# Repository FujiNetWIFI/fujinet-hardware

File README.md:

# FujiNet Hardware

Hardware design files for FujiNet Retro Computer WiFi Adapter

# License

This project is released under the CERN OHL v2.0.

# Notice

Licensees must place a link to the FujiNet project github site, github.com/FujiNetWIFI OR fujinetwifi.github.io, on any product produced using these designs. Using the PCB silk screen layer is recommended for the link and is already provided on released designs.

# Certification

FujiNet hardware is certified open source by [OSHWA](https://oshwa.org). Certification details are available in the [certification directory](https://certification.oshwa.org/us000651.html) under the UID US000651.

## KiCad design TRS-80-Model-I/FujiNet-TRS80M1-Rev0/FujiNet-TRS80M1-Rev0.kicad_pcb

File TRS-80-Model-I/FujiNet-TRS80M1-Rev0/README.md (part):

# FujiNet-TRS80M1 Rev0

FujiNet for the TRS-80 Model I, in place of the Expansion Interface, on one board in a printed case.
- **RP2354B:** serves the Model I's bus (`fujinet-firmware pico/trs80m1`): 32K of RAM, the EI's interrupt latch and
  heartbeat, its printer port, an FD1771 whose drives are FujiNet slots, the RS-232 board, and the FujiBus pipe at
  D0h.
- **ESP32-S3:** the FujiNet (`fujiversal-trs80m1`) and the RP's USB host.
- **Also on the board:** a microSD, a WS2812 status light, the DIP switches that force the RAM / EI / RS-232 off,
  and a USB-C with a CP2102N bridge, the card's only power.
- **The ribbon:** a 40-wire cable from the keyboard unit's expansion edge to a right-angle box header. Every line
  meets a 3.3 V LVC buffer right at the header:
  - the strobes go through Schmitt triggers;
  - D0-D7 are driven only while RD* or IN* is low, through 75R.

**Status (2026-11-25): board routed on 4 layers, JLCPCB and PCBWay packages generated, every gate passing, printed case
drawn. Nothing has been built yet.**
- **Fixed since PR #72:**
  - PR #72 wired header pin n to edge pin n, which no straight ribbon can give: Tandy numbers the edge as the mirror
    image of an IDC connector. The header now carries the edge pins swapped in pairs (*The expansion edge and the header*).
  - The 30 bus inputs are now pulled up to +3V3_RP instead of down.
  - Don't build PR #72's files.
- **Board:** 4 layers, 100 x 76 mm, an M3 hole in each corner. Assembled by JLCPCB or PCBWay, top side: 107 SMD
  parts and the through-hole box header.
- **Firmware:** the schematic implements `pico/trs80m1/firmware/include/m1_card.h`, as it stands in the bring-up's
  dev tree (`~/Workspace/fn-trs80m1`, not on fujinet-firmware master yet). The changes it still needs are under
  *Firmware changes this board needs*.
- **Header:** checked against four sources for the Model I's expansion edge (`tools/audit/header_pinout.py`).
- **Case:** `case/`, checked in OpenSCAD against every part. Not printed yet.

| Check (2026-11-25) | Result |
|---|---|
| Drawing checks (`gen_sch.py`) | every sheet wired. Crossings: 0 on `rp-core`, `fujinet`, `power`; 1 on `usb` (esptool's auto-program pair, as on the sibling carts); 1 on `m1-bus` (the OE gate's IN* tap past RD*: `docs/design-review-rev0.md` 3) |
| Netlist parity: kicad-cli netlist vs `design.py`, names included | 127 / 127 nets |
| KiCad ERC, all severities (kicad-cli and the KiCad MCP) | 0 errors, 0 warnings |
| `tools/audit/header_pinout.py`: the 40 edge pins against the Tech Ref 26-2103 p.91, the RetroStack rev G replica, the 26-1132 HD-adapter document and TRS-IO M1; the ribbon's pair swap against Fig. 22, the HD adapter's cable table and TRS-IO M1's pad numbers; the footprint against its EasyEDA original; pin 1 on the board | 0 failures (`tools/header_geom.VERIFIED = True`) |
| `tools/check_nets.py`: the netlist vs `m1_card.h`, `fujitrs80m1_rp2354b.h`, `fujiversal-trs80m1.h` | 461 checks, 0 failed; 4 NOTE lines (the firmware changes below) |
| `tools/audit/spice/ribbon.py` (ngspice): the ribbon both ways, 15 and 45 cm | strobes never ring through the Schmitt thresholds; the 75R data drive is clean to 45 cm |
| `tools/audit/margins.py`: levels, loads, contention, read timing (in step with the firmware's `test_timing.c`), power | 27 margins, 0 negative (tightest: +23 ns, a 3.55 MHz speed-up's typical read) |
| Routing | 100 % on 4 layers; 686 vias, 1678 tracks |
| KiCad DRC + schematic parity on the saved zone fills (kicad-cli, and again through the KiCad MCP) | 0 errors, 0 unconnected, 0 parity issues; 3 silk-over-edge warnings (the S3 module's outline at the flush east edge) |
| `tools/check_vias.py`: no via in a foreign SMD pad | 686 vias, 0 failures |
| `tools/audit/layout_checks.py`: the layout's claims measured on the copper | 69 / 69. Covers the regulator corner, decoupling (every bus buffer's within 6 mm), the USB pairs and their skew, the crystal, the exposed pads, the antenna band, the buck loop, and every header line to its buffer (42.5 mm and 2 vias at most) |
| `tools/audit/check_gerbers.py`: the zip itself | 0 failures: outline, the four M3 holes, the header's 40 drills with pads and mask both sides, no copper in the antenna band, nothing past the outline, no plated hole in an In1 / In2 pour of another net (762 holes) |
| `tools/audit/check_fab.py`: JLC and PCBWay BOM / CPL / centroid / drills / order-number text / gerbers / the header gate | all pass |
| JLCPCB CPL rotations (`tools/audit/jlc/`), measured against each LCSC part's EasyEDA footprint | 46 (footprint, LCSC) pairs. The RP2354B, the box header, the DIP switch and every logic part are high confidence. Medium: the 1G11, the AOTA and buck inductors, the TS-1187A, the BAT54C, the USB-C, the TLV62569. Check those in JLC's preview |
| kicad-happy 2.2.1 (`tools/audit/run_sch_audit.sh`, `run_pcb_audit.sh`), triaged in `docs/design-review-rev0.md` | 6 high groups: 4 false positives (keep-out circles, U12 decoupling, the LDO thermal estimate at 4x the real load, the header at the edge by design), 2 accepted (plane gaps beside the header's 40 holes, USB full-speed layer changes) |
| Printed case (`case/`, OpenSCAD) | `check` and `parts_check` empty, `parts_control` not |

## Sheets

Drawn with the FujiNet-StudioII / O2 / ColecoVision toolkit:
- **Wires only:** every connection on a sheet is a wire.
- **Rails:** rails are power symbols (`GND`, `VBUS`, `+5V`, `+3V3`, `+3V3_RP`, `DVDD`).
- **Between sheets:** the sheets join only through hierarchical labels, wired on the root's block diagram.

| Page | Sheet | Contents |
|---|---|---|
| 1 | root | the block diagram: rp-core <-> fujinet (USB_DP / USB_DM, RUN_CTL, BOOTSEL_CTL, S3_EN), fujinet <-> usb (S3_TXD / S3_RXD, S3_EN, S3_IO0); notes |
| 2 | `m1-bus` (A2) | Left to right, one block per buffer group:<br>• the header (drawn in units by group) -> 100k pull-downs -> the buffer -> the RP2354B's GPIO unit for that group, every line one straight wire.<br>• A8-A15 and A0-A7: 74LVC245A, A -> B, always on.<br>• D0-D7: 75R, then the 74LVC245A turned round, DIR = DRIVE (GP28) and /OE from the 74LVC1G11 under it (DRIVE . RD* . IN*).<br>• RD* IN* INTAK* and SYSRES* OUT* WR*: two 74LVC3G17 Schmitt receivers.<br>• INT* WAIT*: the 74LVC2G07, pulled up on the RP side.<br>• The logic-analyser header, one unit per probed line.<br>• The DIP switches, LED and debug-UART pads |
| 3 | `rp-core` | the RP2354B's core unit: a capacitor at every supply pin, Raspberry Pi's regulator corner, crystal, SWD, RUN / BOOTSEL / RESET (the BAT54C to S3 EN), the USB 27R pair out to the S3 |
| 4 | `fujinet` | ESP32-S3-WROOM-1-N16R8, its EN RC and buttons, microSD, WS2812 |
| 5 | `usb` | USB-C, USBLC6-2SC6, CP2102N, esptool's auto-program pair |
| 6 | `power` | VBUS -> 1.1 A resettable fuse -> +5V; the RP's AP2112K LDO (+3V3_RP); the S3's TLV62569 buck (+3V3); rail test pads |

## The expansion edge and the header

40 contacts, two rows of 20 at 0.100", on a straight 40-wire IDC ribbon:
- **The Model I end:** a 40-way card-edge IDC connector (3M 3464-series or equivalent) on the keyboard unit's edge.
- **This board's end:** a 2x20 IDC socket on the box header.

**Tandy numbers the edge as the mirror image of that connector**, so the edge pins reach the header swapped in pairs:
header 1 = edge 2, header 2 = edge 1, header 3 = edge 4, and so on.
- Tech Ref Fig. 22, seen from the rear: odd pins on top, pin 1 at the **left**. Tandy's own EI floppy and printer
  edges have pin 1 at the top **right**.
- Buzbee / Fosdick: the expansion port "is configured opposite to other connectors on the expansion interface board".
  Plugged Tandy's way (stripe right, cable down), "the pin 1 stripe will actually connect to pin 39".
- TRS-IO M1 numbers its own edge pads the same way as this header (pad 1 SYSRES*, pad 2 RAS*).

Edge numbers are Tandy's:

| Header | Edge | Signal | Card | Header | Edge | Signal | Card |
|---|---|---|---|---|---|---|---|
| 1 | 2 | SYSRES* | 3G17 -> GP29 | 21 | 22 | D1 | 75R, '245 <-> GP17 |
| 2 | 1 | RAS* | open | 22 | 21 | INT* | GP30 -> 2G07 (OD) |
| 3 | 4 | A10 | '245 -> GP10 | 23 | 24 | D6 | 75R, '245 <-> GP22 |
| 4 | 3 | CAS* | open | 24 | 23 | TEST* | open (floats the buses) |
| 5 | 6 | A13 | '245 -> GP13 | 25 | 26 | D3 | 75R, '245 <-> GP19 |
| 6 | 5 | A12 | '245 -> GP12 | 26 | 25 | A0 | '245 -> GP0 |
| 7 | 8 | GND | GND | 27 | 28 | D5 | 75R, '245 <-> GP21 |
| 8 | 7 | A15 | '245 -> GP15 | 28 | 27 | A1 | '245 -> GP1 |
| 9 | 10 | A14 | '245 -> GP14 | 29 | 30 | D0 | 75R, '245 <-> GP16 |
| 10 | 9 | A11 | '245 -> GP11 | 30 | 29 | GND | GND |
| 11 | 12 | OUT* | 3G17 -> GP27 | 31 | 32 | D2 | 75R, '245 <-> GP18 |
| 12 | 11 | A8 | '245 -> GP8 | 32 | 31 | A4 | '245 -> GP4 |
| 13 | 14 | INTAK* | 3G17 -> GP32 | 33 | 34 | A3 | '245 -> GP3 |
| 14 | 13 | WR* | 3G17 -> GP24 | 34 | 33 | WAIT* | GP31 -> 2G07 (OD) |
| 15 | 16 | MUX | open | 35 | 36 | A7 | '245 -> GP7 |
| 16 | 15 | RD* | 3G17 -> GP25 | 36 | 35 | A5 | '245 -> GP5 |
| 17 | 18 | D4 | 75R, '245 <-> GP20 | 37 | 38 | A6 | '245 -> GP6 |
| 18 | 17 | A9 | '245 -> GP9 | 38 | 37 | GND | GND |
| 19 | 20 | D7 | 75R, '245 <-> GP23 | 39 | 40 | A2 | '245 -> GP2 |
| 20 | 19 | IN* | 3G17 -> GP26 | 40 | 39 | +5V / GND | **open** (+5V on boards A-E, GND on G) |

**Sources** (2026-11-24; `tools/audit/header_pinout.py` has them):
- the TRS-80 Technical Reference Handbook (Radio Shack 26-2103) p.91 table and Fig. 22;
- RetroStack's KiCad replica of the rev G keyboard-unit board (its edge netlist, and the part driving each pin);
- the Tandy 26-1132 hard-disk adapter document;
- TRS-IO M1 v1.4.

All four agree on every pin but 39, which Tandy's own text says Level II machines ground and the replicas show as +5V
on boards A-E. `header_pinout.py` also derives the pair swap from Fig. 22 and the connector, and checks it against
Buzbee / Fosdick's adapter table (the same map, plugged the other way up) and TRS-IO M1's pad numbers.

**What drives the edge** (the replica, and Tech Ref pp.15-18):
- A0-A15, RD*, WR*, IN*, OUT*, RAS*, CAS* and MUX come from 74LS367s ("one TTL load" each).
- SYSRES* comes from an LS02, INTAK* from an LS32.
- INT*, WAIT* and TEST* go straight to the Z80, each with a 4.7k pull-up.
- D0-D7 is the keyboard unit's internal data bus, driven by it except while the Z80 reads.
- The card puts one LVC input and a 100k pull-up to +3V3_RP on each line (`margins.py`). Unplugged, or with the Model I
  off, every line idles high: the strobes and SYSRES* inactive. With the Model I on and the card unpowered, the
  pull-ups back-feed its RP rail about 1 mA, too little to start anything.

**The header:** XFCN BH254R-40P (Ckmtw B-3000R40P-0110 fits the same holes), a right-angle shrouded 2x20.
- It lies along the west edge, its mouth flush with the board edge (0.24 mm past it), the key up.
- The odd pins are on its inboard row, **pin 1 (SYSRES*, edge pin 2) at the south end** by the PIN 1 / STRIPE arrow.

## The cable

**Buy or make** a straight 40-wire flat ribbon, **15 cm** (Tandy's EI cable was 6 in; no more than 30 cm):
- the Model I end: a 40-way 0.100" card-edge IDC connector (3M 3464-0000 or equivalent, for 1.4-1.8 mm boards);
- this board's end: a 2x20 IDC socket;
- both crimped with the red stripe (wire 1) at their pin-1 marks.

**On the Model I, the stripe goes at the left, seen from the rear** (the end of edge pins 1 and 2). The edge has no key slot.
- This is upside down from Tandy's own cables: the ribbon leaves the connector at the top. Wire 1 meets edge pin 2
  (bottom row), wire 2 edge pin 1.
- **Plugged Tandy's way round (stripe right), the card's grounds hold WAIT*, OUT* and A10 low.**
- To plug it Tandy's way round instead, crimp the socket end with its stripe at header pin 40, the north end.

**Before powering anything, with a meter and the Model I off:**
1. The cable alone: header pin 1 to the card-edge connector's contact at its stripe end, and header pin 40 to the
   contact at the far end on the other row. This shows the ribbon is straight.
2. With the connector on the keyboard unit: header pins 7, 30 and 38 to the Model I's ground. All three must ring.

To keep a real Expansion Interface too:
- Crimp a third connector (the EI's card-edge) onto the same ribbon.
- Plug it onto the EI the same way round as the Model I end: the stripe at the end of the EI edge's pins 1-2.
- Set the DIP switches to force off whatever the EI provides.

## RP2354B pin map

Exactly `m1_card.h`, plus INTAK* on GP32. `tools/check_nets.py` reads the dev tree and checks every pin.

| GPIO | Net | Goes to |
|---|---|---|
| 0-15 | RP_A0-A15 | the address 74LVC245As' B ports (`M1_PIN_A0` 0: `addr = pins & 0xFFFF`) |
| 16-23 | RP_D0-D7 | the data 74LVC245A's A port (`M1_PIN_D0` 16) |
| 24 / 25 / 26 / 27 | WR* / RD* / IN* / OUT* | the 74LVC3G17s (RD* on an odd pin: PWM-B counts it) |
| 28 | DRIVE | the data '245's DIR (1 = onto the bus) and the 74LVC1G11; 4.7k pull-down (RP2350-E9: under 8.2k) |
| 29 | SYSRES* | 74LVC3G17 |
| 30 / 31 | INT* / WAIT* | 74LVC2G07 inputs (low = assert), 10k pull-ups: released through reset |
| 32 | INTAK* | 74LVC3G17 (no firmware macro yet) |
| 33 / 34 / 35 | DIP_RAM / DIP_EI / DIP_RS232 | the DIP switches to GND (closed forces it off), 10k pull-ups (`M1_PIN_DIP0` 33) |
| 44 / 45 | DBG_TX / DBG_RX | test pads, UART, 3.3 V |
| 47 | RP_LED | 680R, red LED |
| QSPI | QSPI_SS | the flash is in the package; QSPI_SS is the BOOTSEL strap |
| USB | RP_USB_DP / DM | 27R -> the ESP32-S3's USB host (IO20 / IO19), on the board |
| RUN, QSPI_SS | | 10k pull-ups; RESET / BOOTSEL buttons; 1k from S3 IO4 / IO5 |

**The bus side.**
- **The data transceiver:** /OE is DRIVE . RD* . IN*, taken from the Schmitt receivers' outputs.
  - With DRIVE low it listens (the RP sees every write).
  - With DRIVE high it drives only while a read strobe is low, and lets go at the strobe's rising edge whatever core1 is doing.
- **The 75R on each data line:** it source-terminates the ribbon and limits the overlap current to ~31 mA when the
  keyboard unit takes the bus back.
- **Power and pulls:** every buffer runs at 3.3 V from the RP's LDO, so the RP never sees 5 V. LVC inputs are
  5 V-tolerant with Ioff, so a powered card never back-feeds a Model I that is off, and the reverse.

## ESP32-S3 pin map

`include/pinmap/fujiversal-trs80m1.h` (SD 38-41, UART0 43/44, LED strip 48), plus what every on-cart S3 board adds:

| S3 pin | Net | Goes to |
|---|---|---|
| IO19 / IO20 | USB_DM / USB_DP | the RP2354B's USB through its 27R (the S3 is the host) |
| IO38 / 39 / 40 / 41 | SD_MOSI / SCK / MISO / CS | microSD (SPI), 10k pull-ups on CS, DO, DAT1, DAT2 |
| IO42 | SD_CD | card detect, 10k pull-up (low = card in) |
| IO48 | LED_STRIP | 330R -> WS2812B-2020 (on +5V; VIH 2.7 V takes 3.3 V data) |
| TXD0 / RXD0 | S3_TXD / S3_RXD | CP2102N |
| IO4 / IO5 | RUN_CTL / BOOTSEL_CTL | 1k -> RP RUN / QSPI_SS: the S3 can reset the RP into its USB boot ROM |
| EN / IO0 | S3_EN / S3_IO0 | EN RC (10k / 1 uF), RESET (through the BAT54C), the S3 RST and BOOT buttons, the auto-program pair |

## Power

The Model I's edge carries no supply the card can use, so the card runs from its USB-C:
- pin 39 is +5V only on keyboard boards A-E;
- Tandy warns against loading it.

| Rail | Source | Feeds |
|---|---|---|
| `VBUS` | USB-C (USBLC6, 1 uF + 100 nF) | the fuse, the CP2102N's VBUS sense |
| `+5V` | VBUS through a 1.1 A hold / 2.2 A trip resettable fuse | the buck, the RP LDO, the WS2812 |
| `+3V3` | TLV62569 2 A buck, 3.33 V (100k / 22k), 2.2 uH | ESP32-S3, CP2102N, microSD |
| `+3V3_RP` | AP2112K-3.3 LDO | every RP2354B supply pin and all seven bus buffers |
| `DVDD` | RP2350 core SMPS (3.3 uH) | RP core, 1.1 V |

**Load:** ~0.53 A peak at 5 V in WiFi bursts (`margins.py`). Use a USB-C charger of 1 A or more. A PC's USB 2.0 port
(0.5 A) may sag during bursts.

## Layout

- **Stack (4 layers, JLC04161H-7628):**
  - F.Cu: signals + GND pour.
  - In1: GND.
  - In2: +5V, with a +3V3_RP island (the RP, its LDO and every bus buffer) and a +3V3 island (the east third: the S3, the CP2102N, the microSD).
  - B.Cu: signals + GND pour.
- **Placement (`tools/placement.py`):**
  - **West edge:** the box header, mouth outward.
  - **Bus column:** every buffer within ~15 mm of its header pins, in the header's order. The A0-A7 receiver north, the data transceiver with its 75R and pull-up arrays in the middle, the A8-A15 receiver south. The Schmitt receivers, the INT / WAIT driver and the OE gate east of them.
  - **Centre:** the RP2354B at rotation 0, its bus pins on its west and south sides, with FujiNet-StudioII / O2 Rev0's macro and Raspberry Pi's regulator corner turned with it.
  - **East edge:** the ESP32-S3, its antenna flush with the edge over a strip with no copper on any layer.
  - **North edge:** the USB-C and its ESD, fuse and CP2102N; the buck north-east.
  - **South edge:** the microSD, the DIP switches, RESET and BOOTSEL, and the unfitted logic-analyser header.
- **Deterministic copper:**
  - Raspberry Pi's regulator corner (`tools/rpi_core_graft.sexpr`);
  - the under-package +3V3_RP / DVDD rings (`gen_pcb.rp_support`);
  - the north-side capacitor links;
  - the core-rail pad's link.
- **Routing:** Freerouting, the grid finisher, clean-up, GND stitching, fills, DRC (`tools/route_board.sh`).
- **The board is not reproduced by `LAYOUT=1` alone.**
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
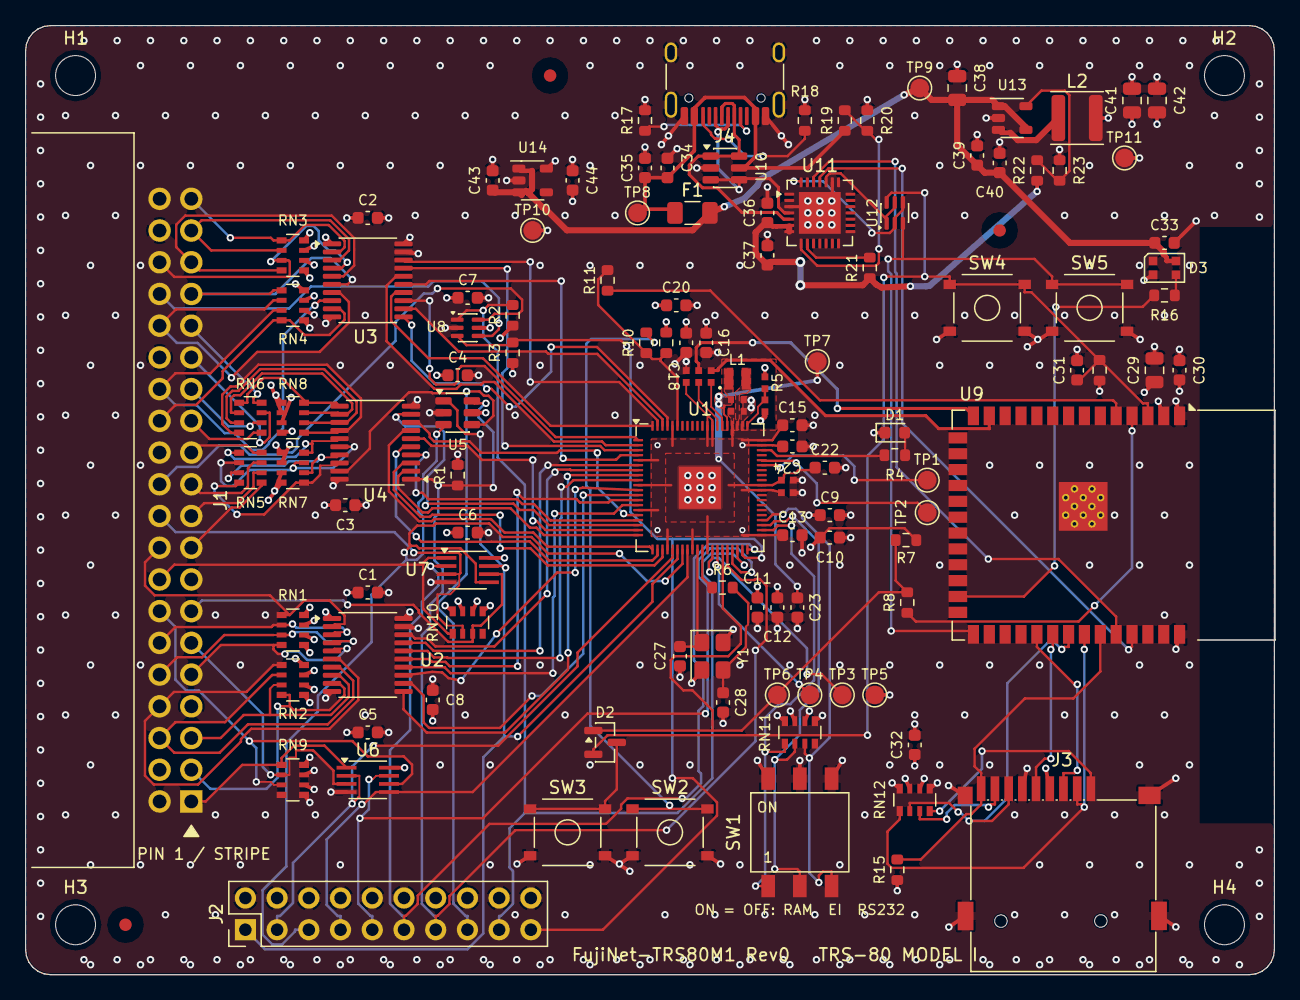
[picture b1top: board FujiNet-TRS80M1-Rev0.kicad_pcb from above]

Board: 4 copper layers, 100.0 x 76.0 mm, 127 parts (0 on the bottom side), 127 nets.

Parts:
C1, C2, C3, C4, C5, C6, C7, C9, C10, C11, C12, C13, C15, C16, C17, C19, C22, C23, C30, C33, C35, C36, C40: 100nF; C_0603_1608Metric
C8, C20, C32, C39: 10uF; C_0603_1608Metric
C14, C18, C24: 100nF; RPI_C0402
C21, C25: 4.7uF; RPI_C0402_wide
C26: 4.7uF; RPI_C0402
C27, C28: 15pF; C_0603_1608Metric
C29, C38, C41, C42: 22uF; C_0805_2012Metric
C31, C34, C43, C44: 1uF; C_0603_1608Metric
C37: 4.7uF; C_0603_1608Metric
D1: red; LED_0603_1608Metric
D2: BAT54C; SOT-23
D3: WS2812B-2020-V6; LED_WS2812B-2020_PLCC4_2.0x2.0mm
F1: 1.1A; Fuse_1206_3216Metric
FID1, FID2, FID3: Fiducial_1mm_Mask2mm
H1, H2, H3, H4: MountingHole_3.2mm_NPTH
J1: TRS-80 Model I expansion; IDC-Header_2x20_P2.54mm_Horizontal_BH254R-40P
J2: LA probe; PinHeader_2x10_P2.54mm_Vertical
J3: microSD; TF-SMD_TF-015
J4: USB-C; USB_C_Receptacle_HRO_TYPE-C-31-M-12
L1: 3.3uH; RPI_L_AOTA-B201610S3R3
L2: 2.2uH; L_Sunlord_SWPA4030S
R1: 4.7k; R_0603_1608Metric
R2, R3, R7, R9, R14, R15: 10k; R_0603_1608Metric
R4: 680R; R_0603_1608Metric
R5: 33R; RPI_R0402
R6, R8, R10, R11, R21: 1k; R_0603_1608Metric
R12, R13: 27R; RPI_R0402
R16: 330R; R_0603_1608Metric
R17, R18: 5.1k; R_0603_1608Metric
R19, R23: 22k; R_0603_1608Metric
R20: 47k; R_0603_1608Metric
R22: 100k; R_0603_1608Metric
RN1, RN2, RN3, RN4, RN7, RN8, RN9, RN10: 4x100k; R_Array_Convex_4x0603
RN5, RN6: 4x75R; R_Array_Convex_4x0603
RN11, RN12: 4x10k; R_Array_Convex_4x0603
SW1: RAM EI RS232; SW_DIP_SPSTx03_SMD_P2.54mm_HX
SW2: BOOTSEL; SW_SPST_TS-1187A
SW3: RESET; SW_SPST_TS-1187A
SW4: S3_RST; SW_SPST_TS-1187A
SW5: S3_BOOT; SW_SPST_TS-1187A
TP1: DBG_TX; TestPoint_Pad_D1.5mm
TP2: DBG_RX; TestPoint_Pad_D1.5mm
TP3: SWCLK; TestPoint_Pad_D1.5mm
TP4: SWDIO; TestPoint_Pad_D1.5mm
TP5: GND; TestPoint_Pad_D1.5mm
TP6: RUN; TestPoint_Pad_D1.5mm
TP7: DVDD; TestPoint_Pad_D1.5mm
TP8: VBUS; TestPoint_Pad_D1.5mm
TP9: +5V; TestPoint_Pad_D1.5mm
TP10: +3V3_RP; TestPoint_Pad_D1.5mm
TP11: +3V3; TestPoint_Pad_D1.5mm
U1: RP2354B; QFN-80-1EP_10x10mm_P0.4mm_EP3.4x3.4mm
U2, U3, U4: 74LVC245A; TSSOP-20_4.4x6.5mm_P0.65mm
U5: 74LVC1G11; SOT-23-6
U6, U7: 74LVC3G17; SSOP-8_2.95x2.8mm_P0.65mm
U8: 74LVC2G07; SOT-363_SC-70-6
U9: ESP32-S3-WROOM-1-N16R8; ESP32-S3-WROOM-1
U10: USBLC6-2SC6; SOT-23-6
U11: CP2102N-A02-GQFN28; QFN-28-1EP_5x5mm_P0.5mm_EP3.35x3.35mm
U12: UMH3N; SOT-363_SC-70-6
U13: TLV62569DBV; SOT-23-5
U14: AP2112K-3.3; SOT-23-5
Y1: 12MHz; Crystal_SMD_3225-4Pin_3.2x2.5mm

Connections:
+3V3: C29.1, C30.1, C32.1, C36.1, C37.1, C41.1, C42.1, J3.4, L2.2, R14.1, R15.1, R21.1, R22.1, RN12.5, RN12.6, RN12.7, RN12.8, TP11.1, U9.2, U11.6, U11.7
+3V3_RP: C1.1, C2.1, C3.1, C4.1, C5.1, C6.1, C7.1, C8.1, C9.1, C10.1, C11.1, C12.1, C13.1, C14.1, C15.1, C16.1, C17.1, C18.1, C19.1, C20.1, C21.1, C44.1, R2.1, R3.1, R5.1, R7.1, R9.1, RN1.5, RN1.6, RN1.7, RN1.8, RN2.5, RN2.6, RN2.7, RN2.8, RN3.5, RN3.6, RN3.7, RN3.8, RN4.5, RN4.6, RN4.7, RN4.8, RN7.5, RN7.6, RN7.7, RN7.8, RN8.5, RN8.6, RN8.7, RN8.8, RN9.5, RN9.6, RN9.7, RN9.8, RN10.5, RN10.6, RN10.7, RN10.8, RN11.5, RN11.6, RN11.7, RN11.8, TP10.1, U1.5, U1.15, U1.24, U1.29, U1.41, U1.50, U1.59, U1.60, U1.64, U1.68, U1.69, U1.76, U2.1, U2.20, U3.1, U3.20, U4.20, U5.5, U6.8, U7.8, U8.5, U14.5
+5V: C33.1, C38.1, C39.1, C40.1, C43.1, D3.4, F1.2, TP9.1, U13.1, U13.4, U14.1, U14.3
/BOOTSEL_CTL: R11.1, U9.5
/RUN_CTL: R8.1, U9.4
/S3_EN: C31.1, D2.2, R14.2, SW4.1, U9.3, U12.6
/S3_IO0: SW5.1, U9.27, U12.3
/S3_RXD: U9.36, U11.26
/S3_TXD: U9.37, U11.25
/USB_DM: R13.1, U9.13
/USB_DP: R12.1, U9.14
/fujinet/LED_STRIP: R16.1, U9.25
/fujinet/SD_CD: J3.9, R15.2, U9.35
/fujinet/SD_CS: J3.2, RN12.1, U9.34
/fujinet/SD_DAT1: J3.8, RN12.3
/fujinet/SD_DAT2: J3.1, RN12.4
/fujinet/SD_MISO: J3.7, RN12.2, U9.33
/fujinet/SD_MOSI: J3.3, U9.31
/fujinet/SD_SCK: J3.5, U9.32
/fujinet/WS_DIN: D3.3, R16.2
/m1-bus/BUF_OE_N: J2.15, U4.19, U5.4
/m1-bus/DBG_RX: TP2.1, U1.56
/m1-bus/DBG_TX: TP1.1, U1.55
/m1-bus/DIP_EI: RN11.2, SW1.2, U1.43
/m1-bus/DIP_RAM: RN11.1, SW1.1, U1.42
/m1-bus/DIP_RS232: RN11.3, SW1.3, U1.44
/m1-bus/DRIVE: J2.13, R1.1, U1.36, U4.1, U5.6
/m1-bus/M1_A0: J1.26, RN4.4, U3.9
/m1-bus/M1_A1: J1.28, RN4.3, U3.8
/m1-bus/M1_A2: J1.39, RN3.1, U3.2
/m1-bus/M1_A3: J1.33, RN4.1, U3.6
/m1-bus/M1_A4: J1.32, RN4.2, U3.7
/m1-bus/M1_A5: J1.36, RN3.3, U3.4
/m1-bus/M1_A6: J1.37, RN3.2, U3.3
/m1-bus/M1_A7: J1.35, RN3.4, U3.5
/m1-bus/M1_A8: J1.12, RN1.2, U2.3
/m1-bus/M1_A9: J1.18, RN1.1, U2.2
/m1-bus/M1_A10: J1.3, RN2.4, U2.9
/m1-bus/M1_A11: J1.10, RN1.3, U2.4
/m1-bus/M1_A12: J1.6, RN2.2, U2.7
/m1-bus/M1_A13: J1.5, RN2.3, U2.8
/m1-bus/M1_A14: J1.9, RN1.4, U2.5
/m1-bus/M1_A15: J1.8, RN2.1, U2.6
/m1-bus/M1_D0: J1.29, RN6.3
/m1-bus/M1_D1: J1.21, RN5.3
/m1-bus/M1_D2: J1.31, RN6.4
/m1-bus/M1_D3: J1.25, RN6.1
/m1-bus/M1_D4: J1.17, RN5.1
/m1-bus/M1_D5: J1.27, RN6.2
/m1-bus/M1_D6: J1.23, RN5.4
/m1-bus/M1_D7: J1.19, RN5.2
/m1-bus/M1_DS0: RN6.6, RN8.3, U4.12
/m1-bus/M1_DS1: RN5.6, RN7.3, U4.16
/m1-bus/M1_DS2: RN6.5, RN8.4, U4.11
/m1-bus/M1_DS3: RN6.8, RN8.1, U4.14
/m1-bus/M1_DS4: RN5.8, RN7.1, U4.18
/m1-bus/M1_DS5: RN6.7, RN8.2, U4.13
/m1-bus/M1_DS6: RN5.5, RN7.4, U4.15
/m1-bus/M1_DS7: RN5.7, RN7.2, U4.17
/m1-bus/M1_INTAK_N: J1.13, RN10.3, U7.6
/m1-bus/M1_INT_N: J1.22, U8.6
/m1-bus/M1_IN_N: J1.20, RN10.2, U7.3
/m1-bus/M1_OUT_N: J1.11, RN9.2, U6.3
/m1-bus/M1_RD_N: J1.16, RN10.1, U7.1
/m1-bus/M1_SYSRES_N: J1.1, RN9.1, U6.1
/m1-bus/M1_WAIT_N: J1.34, U8.4
/m1-bus/M1_WR_N: J1.14, RN9.3, U6.6
/m1-bus/RP_A0: U1.77, U3.11
/m1-bus/RP_A1: U1.78, U3.12
/m1-bus/RP_A2: U1.79, U3.18
/m1-bus/RP_A3: U1.80, U3.14
/m1-bus/RP_A4: U1.1, U3.13
/m1-bus/RP_A5: U1.2, U3.16
/m1-bus/RP_A6: U1.3, U3.17
/m1-bus/RP_A7: U1.4, U3.15
/m1-bus/RP_A8: U1.6, U2.17
/m1-bus/RP_A9: U1.7, U2.18
/m1-bus/RP_A10: U1.8, U2.11
/m1-bus/RP_A11: U1.9, U2.16
/m1-bus/RP_A12: U1.11, U2.13
/m1-bus/RP_A13: U1.12, U2.12
/m1-bus/RP_A14: U1.13, U2.15
/m1-bus/RP_A15: U1.14, U2.14
/m1-bus/RP_D0: U1.16, U4.8
/m1-bus/RP_D1: U1.17, U4.4
/m1-bus/RP_D2: U1.18, U4.9
/m1-bus/RP_D3: U1.19, U4.6
/m1-bus/RP_D4: U1.20, U4.2
/m1-bus/RP_D5: U1.21, U4.7
/m1-bus/RP_D6: U1.22, U4.5
/m1-bus/RP_D7: U1.23, U4.3
/m1-bus/RP_INTAK_N: J2.11, U1.40, U7.2
/m1-bus/RP_INT_N: J2.17, R2.2, U1.38, U8.1
/m1-bus/RP_IN_N: J2.5, U1.27, U5.3, U7.5
/m1-bus/RP_LED: R4.1, U1.58
/m1-bus/RP_LED_A: D1.2, R4.2
/m1-bus/RP_OUT_N: J2.7, U1.28, U6.5
/m1-bus/RP_RD_N: J2.1, U1.26, U5.1, U7.7
/m1-bus/RP_SYSRES_N: J2.9, U1.37, U6.7
/m1-bus/RP_WAIT_N: J2.19, R3.2, U1.39, U8.3
/m1-bus/RP_WR_N: J2.3, U1.25, U6.2
/power/BUCK_FB: R22.2, R23.1, U13.5
/power/BUCK_SW: L2.1, U13.3
/rp-core/BOOTSEL_BTN: R10.2, SW2.1
/rp-core/QSPI_SS: R9.2, R10.1, R11.2, U1.75
/rp-core/RP_LX: L1.2, U1.63
/rp-core/RP_USB_DM: R13.2, U1.66
/rp-core/RP_USB_DP: R12.2, U1.67
/rp-core/RST_BTN: D2.3, SW3.1
/rp-core/RUN: D2.1, R7.2, R8.2, TP6.1, U1.35
/rp-core/SWCLK: TP3.1, U1.33
/rp-core/SWDIO: TP4.1, U1.34
/rp-core/VREG_AVDD: C26.1, R5.2, U1.61
/rp-core/XIN: C27.1, U1.30, Y1.1
/rp-core/XOUT: R6.1, U1.31
/rp-core/XOUT_Y: C28.1, R6.2, Y1.3
/usb/CC1: J4.A5, R17.1
/usb/CC2: J4.B5, R18.1
/usb/CP_RST: R21.2, U11.9
/usb/UART_DTR: U11.28, U12.2, U12.4
/usb/UART_RTS: U11.24, U12.1, U12.5
/usb/UBRG_DM: J4.A7, J4.B7, U10.1, U10.6, U11.5
/usb/UBRG_DP: J4.A6, J4.B6, U10.3, U10.4, U11.4
/usb/VBUS_SNS: R19.2, R20.1, U11.8
DVDD: C22.1, C23.1, C24.1, C25.1, L1.1, TP7.1, U1.10, U1.32, U1.51, U1.65
GND: C1.2, C2.2, C3.2, C4.2, C5.2, C6.2, C7.2, C8.2, C9.2, C10.2, C11.2, C12.2, C13.2, C14.2, C15.2, C16.2, C17.2, C18.2, C19.2, C20.2, C21.2, C22.2, C23.2, C24.2, C25.2, C26.2, C27.2, C28.2, C29.2, C30.2, C31.2, C32.2, C33.2, C34.2, C35.2, C36.2, C37.2, C38.2, C39.2, C40.2, C41.2, C42.2, C43.2, C44.2, D1.1, D3.2, J1.7, J1.30, J1.38, J2.2, J2.4, J2.6, J2.8, J2.10, J2.12, J2.14, J2.16, J2.18, J2.20, J3.6, J3.10, J3.11, J3.12, J3.13, J4.A1, J4.A12, J4.B1, J4.B12, J4.SH, R1.2, R17.2, R18.2, R20.2, R23.2, SW1.4, SW1.5, SW1.6, SW2.2, SW3.2, SW4.2, SW5.2, TP5.1, U1.62, U1.81, U2.10, U2.19, U3.10, U3.19, U4.10, U5.2, U6.4, U7.4, U8.2, U9.1, U9.40, U9.41, U10.2, U11.3, U11.23, U11.29, U13.2, U14.2, Y1.2, Y1.4
VBUS: C34.1, C35.1, F1.1, J4.A4, J4.A9, J4.B4, J4.B9, R19.1, TP8.1, U10.5

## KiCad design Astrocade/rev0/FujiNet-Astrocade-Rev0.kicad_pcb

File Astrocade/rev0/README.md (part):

# FujiNet-Astrocade Rev0

All-in-one **Bally Astrocade FujiNet cartridge**: one board in an Astrocade
cassette shell carrying both halves of the Astrocade FujiNet stack.

- **RP2354A** (RP2350A die + 2 MB flash in the package, QFN-60) runs the
  `fujicade` cart firmware from `fujinet-firmware/pico/astrocade`, board
  **`fujicade_rp2354`**. It serves the 8K cart window and the FujiNet
  mailbox straight off the 5 V bus through its 5 V-tolerant pads, with **no
  level shifters**. The pads tolerate 5 V only while IOVDD is powered, so the
  whole RP runs from its own fast LDO (see *Power*).
- **ESP32-S3-WROOM-1-N16R8** runs the **`fujiversal-astrocade`** build of
  fujinet-firmware. The two chips link **on the board over native USB**: the
  S3 is the USB *host* (IO19/IO20) and the RP a CDC device (VID 0xCafe).
  The S3 embeds the RP image and re-flashes it over PICOBOOT whenever it
  changes (`build_pico.py`).
- **USB-C** carries power plus a CP2102N UART with UMH3N auto-program
  (ESP32-S3-DevKitC-1 style) for flashing the S3.
- **microSD** (push-push, SPI on S3 IO38-41). Card detect on IO42 reads
  **low with a card in** (TF-015 drawing: the CD switch closes to the shell).
- **WS2812B-2020** status LED under a light pipe, on **+5V**: its datasheet
  rates VDD 3.7-5.3 V. VIH min is 2.7 V, so the S3's 3.3 V data drives it
  without a level shifter.
- **Buttons:** top-face **RESET** (SW4, resets the RP and the S3, through a
  printed plunger), **BOOTSEL** pinhole (SW1), and S3 **EN/BOOT** pinholes
  (SW2/SW3). All four are ALPS SKQGABE010 on the TL3342 land (same lead
  pattern; pins 1-2 and 3-4 tied the same way). The TL3342F160QG ran out at JLC
  in 2026-11.

This revision was audited with kicad-happy and the manufacturer datasheets,
and then redone. The schematic, board and fabrication files are all generated
from `tools/` (see *Regenerating*). The audit is
[`docs/design-review-rev0.md`](docs/design-review-rev0.md).

## Schematic

The schematic is drawn the way the later carts' (2600 Rev1, 7800, SMS, 5200) are:
- **every sheet is the board turned edge-left**: board south -> page left, north -> right, west -> top, east -> bottom;
- each part sits where it is on the board, and `tools/sch_place.py` checks the order;
- **every connection on a sheet is a wire**, flowing left to right from the console to the USB-C.

| Page | Sheet | Contents |
|---|---|---|
| 1 | root | The board outline at 2:1 with each sheet's block over its region; the nine signals between sheets wired; notes |
| 2 | `cart-bus` | The 26-land edge **straight into the RP2354A's GPIO unit**: 22 parallel wires (/CCS, A0-A12, D0-D7), no buffers; /CCS pull-up, the VSENSE divider, activity LED, SELFTEST / DBG_TX pads |
| 3 | `rp-core` | The RP2354A's core unit: every supply pin with its capacitor, the core regulator corner, crystal, SWD, RUN / BOOTSEL / RESET, the USB pair to the S3 |
| 4 | `fujinet` | ESP32-S3, EN / BOOT, microSD, WS2812 status LED |
| 5 | `usb` | USB-C, ESD, CP2102N, esptool's auto-program pair |
| 6 | `power` | Console 5 V / USB VBUS diode-OR, 3.3 V buck, RP LDO |

Rails are power symbols (`CONS_5V`, `VBUS`, `+5V`, `+3V3`, `+3V3_RP`, `DVDD`, `GND`). Sheets join only through hierarchical labels, wired on the root. KiCad names the nets:
- `/cart-bus/CA0` for a net local to its sheet;
- `/S3_EN` for a net joined on the root;
- `GND` for a rail.

The names are frozen in `tools/nets.lock` because the routed board carries them. References are frozen in `tools/refs.lock`.

## Edge port

The cassette edge carries **A0-A12, D0-D7, one pre-decoded active-low
Enable (/CCS), +5V and 3x GND**. There is no /RD, /WR, clock or reset, and
the console only ever *reads* the cart. The RP pin map is exactly
`astrocade_cart.h`:

| RP2354A | Net | Edge (Tilton 1-26) |
|---|---|---|
| GP0-GP12 | CA0-CA12 | A0 9, A1 8, A2 7, A3 6, A4 5, A5 4, A6 3, A7 2, A8 24, A9 23, A10 20, A11 19, A12 22 |
| GP13 | CCS_N (10k pull-up to +3V3_RP) | 21 |
| GP14-GP21 | CD0-CD7 | D0 10, D1 11, D2 12, D3 14, D4 15, D5 16, D6 17, D7 18 |
| GP26 | VSENSE: edge +5V (CONS_5V) through 10k/15k (3.0 V; 6 kOhm, below RP2350-E9's 8.2 kOhm) | 25 |
| GP22 / GP27 | SELFTEST / DBG_TX test pads | - |
| GP25 | green activity LED (330R) | - |

`tools/audit/edge_orientation.py` checks the generated board: land 1 is
**east** in KiCad top view, on B.Cu. That matches Tilton's "looking at the
cart slot, pins 1 to 26 left to right" with the cart inserted label-up.

**The unbuffered bus is safe because the firmware gates it.** The core1 loop
serves a read only while `(pins & SERVE_MASK) == SERVE_WANT`: /CCS low
**and** VSENSE high (`FUJICADE_VSENSE_PIN`). VSENSE is sensed on the console
side of the OR diode. So a cart on USB power in an **unpowered** console
never drives D0-D7 into it, and the loop lets go if the console loses power
mid-cycle. The bus pads' pull-downs are disabled (`FUJICADE_BUS_NO_PULLS`,
RP2350-E9).

The S3 pins follow `include/pinmap/fujiversal-astrocade.h`:

| S3 | Function |
|---|---|
| IO38/39/40/41 | SD MOSI / SCK / MISO / CS |
| IO42 | SD card detect (10k pull-up, low = card present) |
| IO48 | WS2812 (330R) |
| IO4 / IO5 | `PIN_RP2040_RUN` / `PIN_RP2040_BOOTSEL`, 1k each to RP RUN / QSPI_SS |
| IO19 / IO20 | USB D- / D+ to the RP (27R series) |
| TXD0 / RXD0 | CP2102N |

**Why RUN/BOOTSEL are direct 1k links.** `fnPicoUpdater::forceBootselViaPins()`
drives these pins **low** to assert and leaves them as inputs when idle. An
NPN driver (as on INTV Rev0) would invert that. Both chips run at 3.3 V
(`+3V3` and `+3V3_RP`), so a series resistor is the whole interface.

## Power

| Rail | Source | Feeds |
|---|---|---|
| `CONS_5V` | edge land 25 | OR diode, VSENSE divider |
| `VBUS` | USB-C (1 uF + 100 nF, ESD) | OR diode, CP2102N VBUS sense |
| `+5V` | SS34 diode-OR of CONS_5V and VBUS | buck, RP LDO, WS2812 |
| `+3V3` | AP63203 3.3 V / 2 A buck (6.8 uH) | ESP32-S3, CP2102N, microSD |
| `+3V3_RP` | **AP2112K-3.3 LDO** | every RP2354A supply: IOVDD x6, QSPI_IOVDD, USB_OTP_VDD, ADC_AVDD, VREG_VIN, VREG_AVDD (33R / 4.7 uF) |
| `DVDD` | RP2350 core SMPS (3.3 uH AOTA) | RP core, 1.1 V |

- **Why the RP has its own LDO.** The RP2350 datasheet says the GPIOs tolerate
  5.5 V "provided IOVDD is powered to 3.3 V" (p.1332). The first Rev0 fed IOVDD
  from the buck. The buck stays off until its UVLO, then soft-starts over
  4 ms, which left the pads unpowered while the console drove the bus. The
  AP2112K sits in dropout while the console rail rises, so +3V3_RP follows it.
  Following 1 V/ms into the rail's 21 uF needs 21 mA, under the 50 mA
  fold-back limit. A hot-plug step would take up to 1.4 ms, but hot-plugging
  isn't supported. Bring-up item 2 scopes it.
- **Supply order.** VREG_VIN and VREG_AVDD must rise together (p.402), and both
  are on the LDO.
- **Headroom.** At a 4.75 V console rail, +5V is at least 4.37 V after the
  diode. That clears the buck (3.8 V), the LDO (3.55 V) and the WS2812
  (3.7 V). There is no 5 V logic on the board. Numbers in
  `tools/audit/por_window.py`.

## Mechanics: a cassette, not a finger cart

A Videocade is a closed cassette-style box lying label-up in an **open-top
well**. The console's 26-contact **blade** (0.100" pitch, about 74 mm wide)
enters a slot in the leading face, under the board. It presses **up** against
gold lands on the **PCB underside**.

The shell is `case/FujiNet-Astrocade-Shell.scad`, and `case/case-spec.md` is
its dimension dossier. The leading section is a stock cart's: 100 mm wide,
12.0 mm thick, with the blade slot, the blade-stop rib 12.86 mm in, and the
board plane. These are measured from Lance F. Squire's printed cart shell
(Thingiverse thing:173532, CC BY). Behind it the shell rises to 15.5 mm. The
USB-C and microSD sit flush with the trailing face, and a hood covers the
antenna. `case/board-anchors.scad` (from the placement) and
`case/board-parts.scad` (from the routed board) feed it. Its `check` view
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
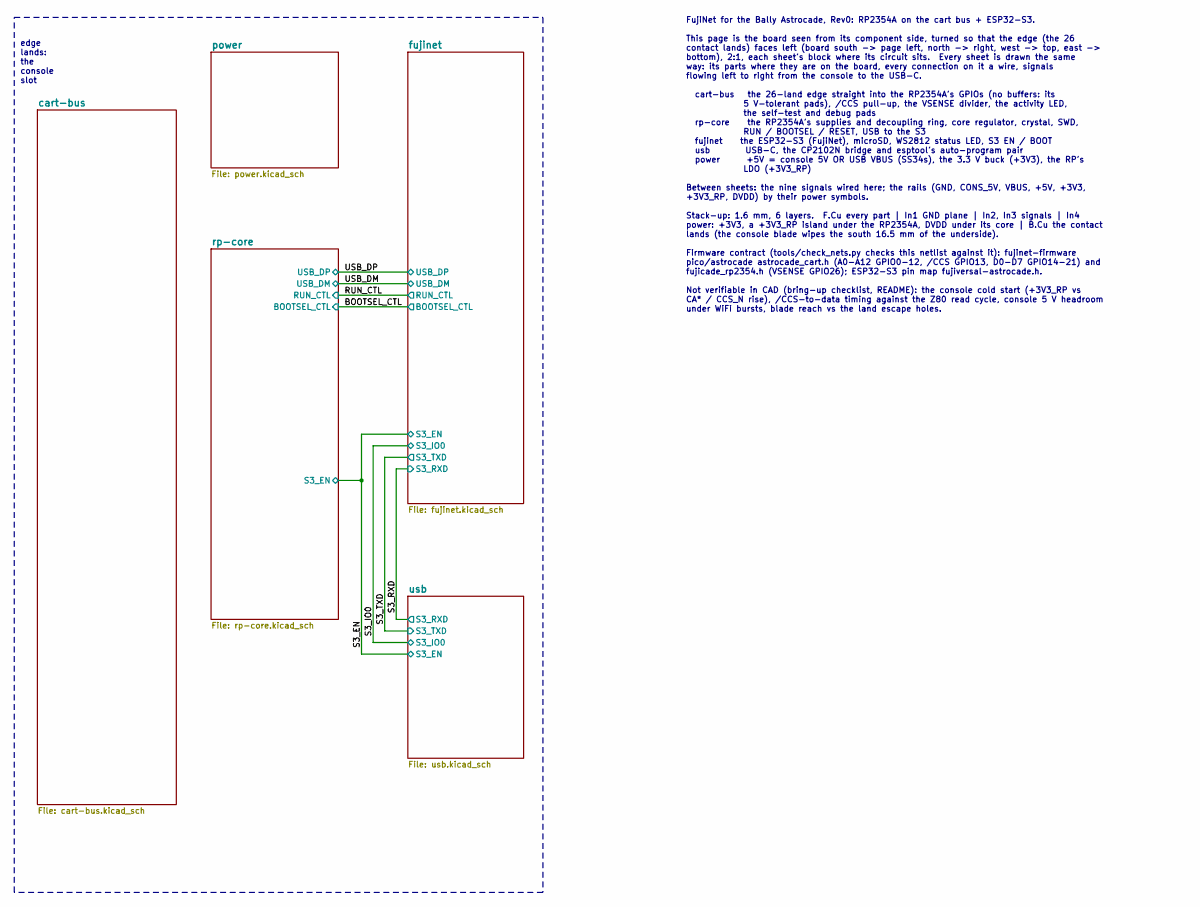
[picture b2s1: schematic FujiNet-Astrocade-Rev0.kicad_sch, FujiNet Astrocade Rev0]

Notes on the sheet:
edge lands: the console slot
FujiNet for the Bally Astrocade, Rev0: RP2354A on the cart bus + ESP32-S3. This page is the board seen from its component side, turned so that the edge (the 26 contact lands) faces left (board south -> page left, north -> right, west -> top, east -> bottom), 2:1, each sheet's block where its circui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

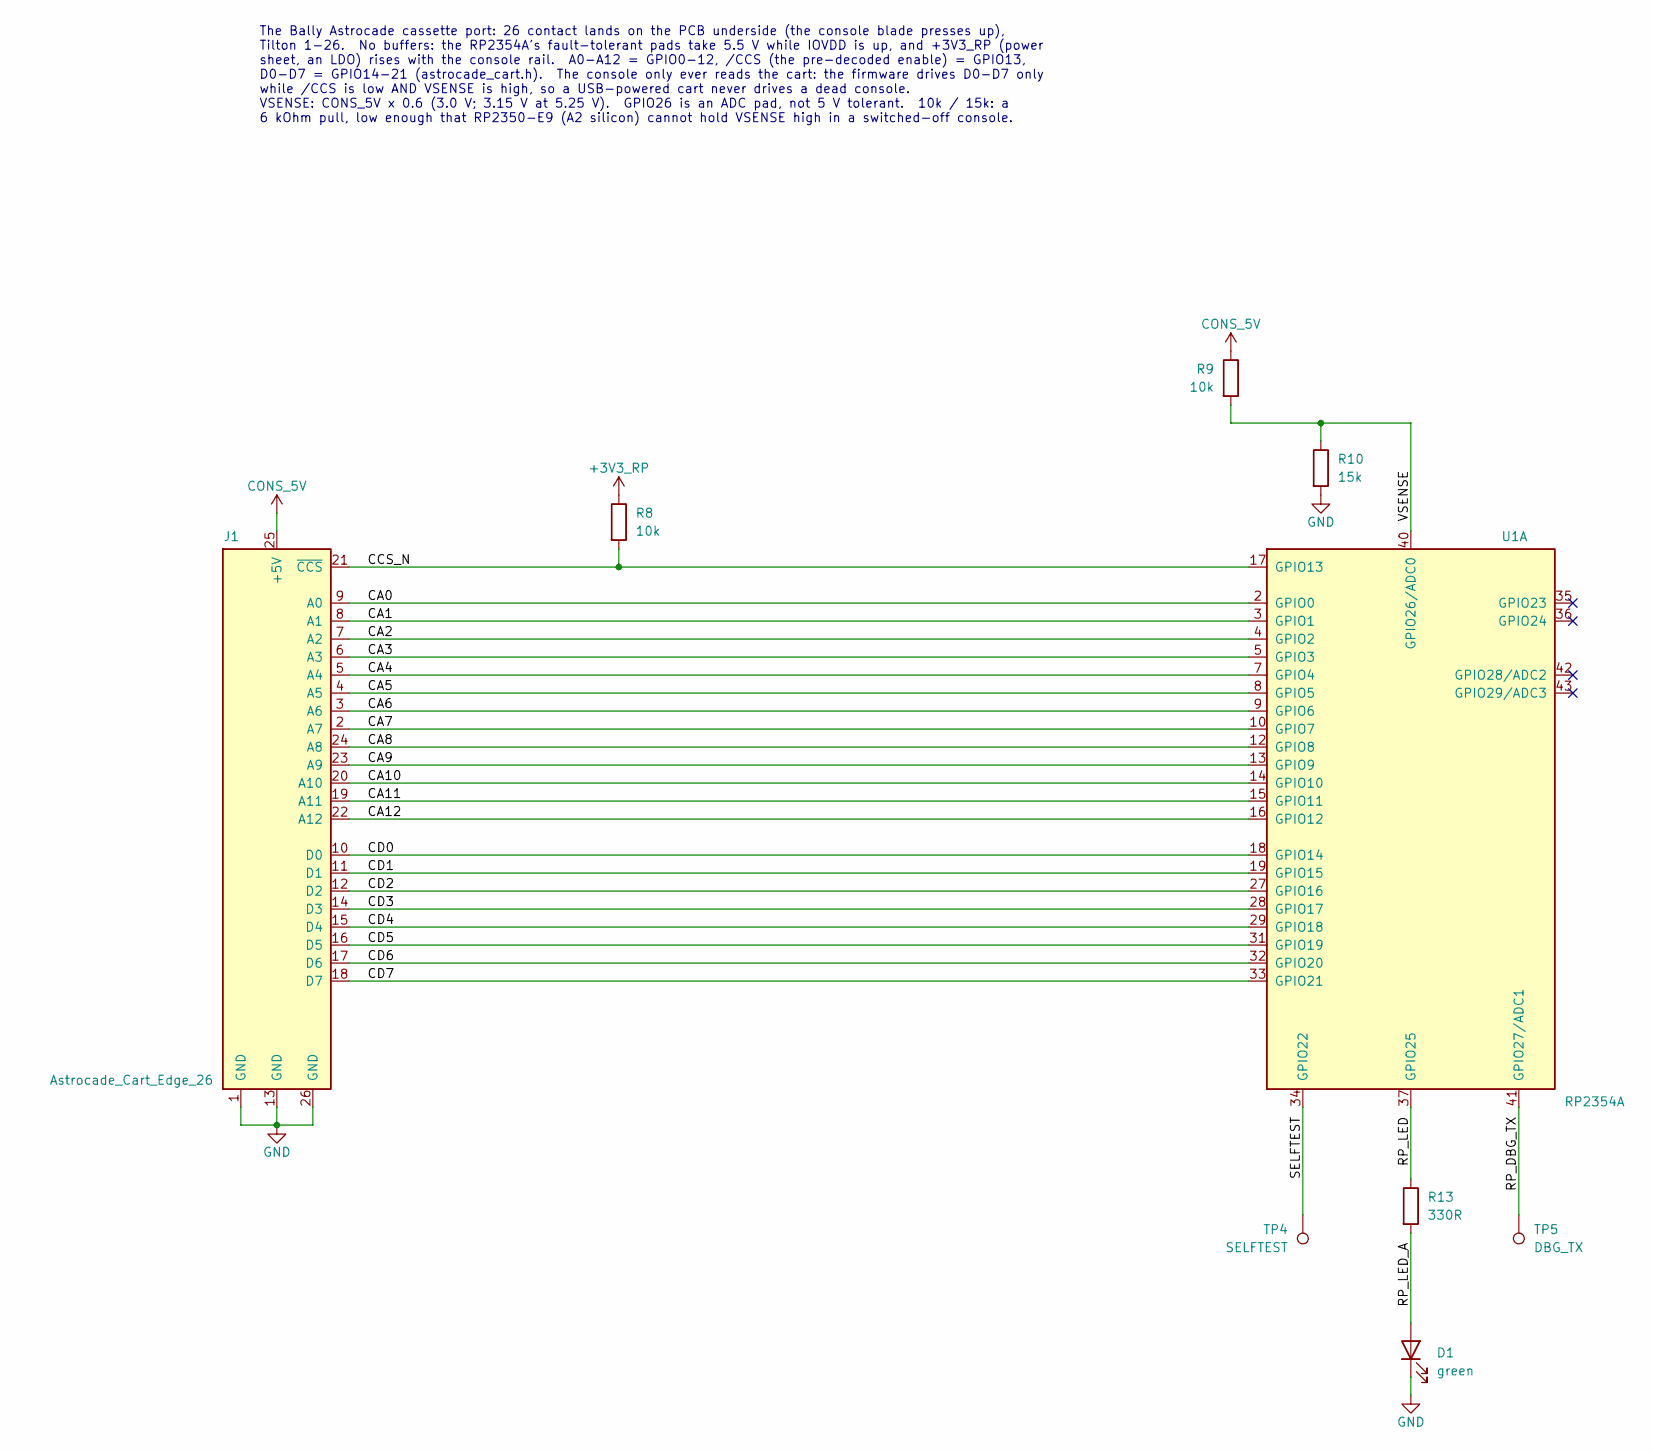
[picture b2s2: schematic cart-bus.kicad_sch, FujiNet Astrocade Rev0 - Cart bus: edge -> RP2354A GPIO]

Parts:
D1: green; LED_0603_1608Metric; MPN KT-0603G; LCSC C12624
J1: Astrocade_Cart_Edge_26
R8, R9: 10k; R_0603_1608Metric; MPN 0603WAF1002T5E; LCSC C25804
R10: 15k; R_0603_1608Metric; MPN 0603WAF1502T5E; LCSC C22809
R13: 330R; R_0603_1608Metric; MPN 0603WAF3300T5E; LCSC C23138
TP4: SELFTEST; TestPoint_Pad_D1.5mm
TP5: DBG_TX; TestPoint_Pad_D1.5mm
U1: RP2354A; RPI_RP2350A_QFN60; MPN RP2354A; LCSC C41378174

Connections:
+3V3_RP: R8.1; also elsewhere on the board
/cart-bus/CA0: J1.9 (A0), U1.2 (GPIO0)
/cart-bus/CA1: J1.8 (A1), U1.3 (GPIO1)
/cart-bus/CA2: J1.7 (A2), U1.4 (GPIO2)
/cart-bus/CA3: J1.6 (A3), U1.5 (GPIO3)
/cart-bus/CA4: J1.5 (A4), U1.7 (GPIO4)
/cart-bus/CA5: J1.4 (A5), U1.8 (GPIO5)
/cart-bus/CA6: J1.3 (A6), U1.9 (GPIO6)
/cart-bus/CA7: J1.2 (A7), U1.10 (GPIO7)
/cart-bus/CA8: J1.24 (A8), U1.12 (GPIO8)
/cart-bus/CA9: J1.23 (A9), U1.13 (GPIO9)
/cart-bus/CA10: J1.20 (A10), U1.14 (GPIO10)
/cart-bus/CA11: J1.19 (A11), U1.15 (GPIO11)
/cart-bus/CA12: J1.22 (A12), U1.16 (GPIO12)
/cart-bus/CCS_N: J1.21 (~CCS), R8.2, U1.17 (GPIO13)
/cart-bus/CD0: J1.10 (D0), U1.18 (GPIO14)
/cart-bus/CD1: J1.11 (D1), U1.19 (GPIO15)
/cart-bus/CD2: J1.12 (D2), U1.27 (GPIO16)
/cart-bus/CD3: J1.14 (D3), U1.28 (GPIO17)
/cart-bus/CD4: J1.15 (D4), U1.29 (GPIO18)
/cart-bus/CD5: J1.16 (D5), U1.31 (GPIO19)
/cart-bus/CD6: J1.17 (D6), U1.32 (GPIO20)
/cart-bus/CD7: J1.18 (D7), U1.33 (GPIO21)
/cart-bus/RP_DBG_TX: TP5.1, U1.41 (GPIO27/ADC1)
/cart-bus/RP_LED: R13.1, U1.37 (GPIO25)
/cart-bus/RP_LED_A: D1.2 (A), R13.2
/cart-bus/SELFTEST: TP4.1, U1.34 (GPIO22)
/cart-bus/VSENSE: R9.2, R10.1, U1.40 (GPIO26/ADC0)
CONS_5V: J1.25 (+5V), R9.1; also elsewhere on the board
GND: D1.1 (K), J1.1 (GND), J1.13 (GND), J1.26 (GND), R10.2; also elsewhere on the board

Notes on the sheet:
The Bally Astrocade cassette port: 26 contact lands on the PCB underside (the console blade presses up), Tilton 1-26. No buffers: the RP2354A's fault-tolerant pads take 5.5 V while IOVDD is up, and +3V3_RP (power sheet, an LDO) rises with the console rail. A0-A12 = GPIO0-12, /CCS (the pre-decoded e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

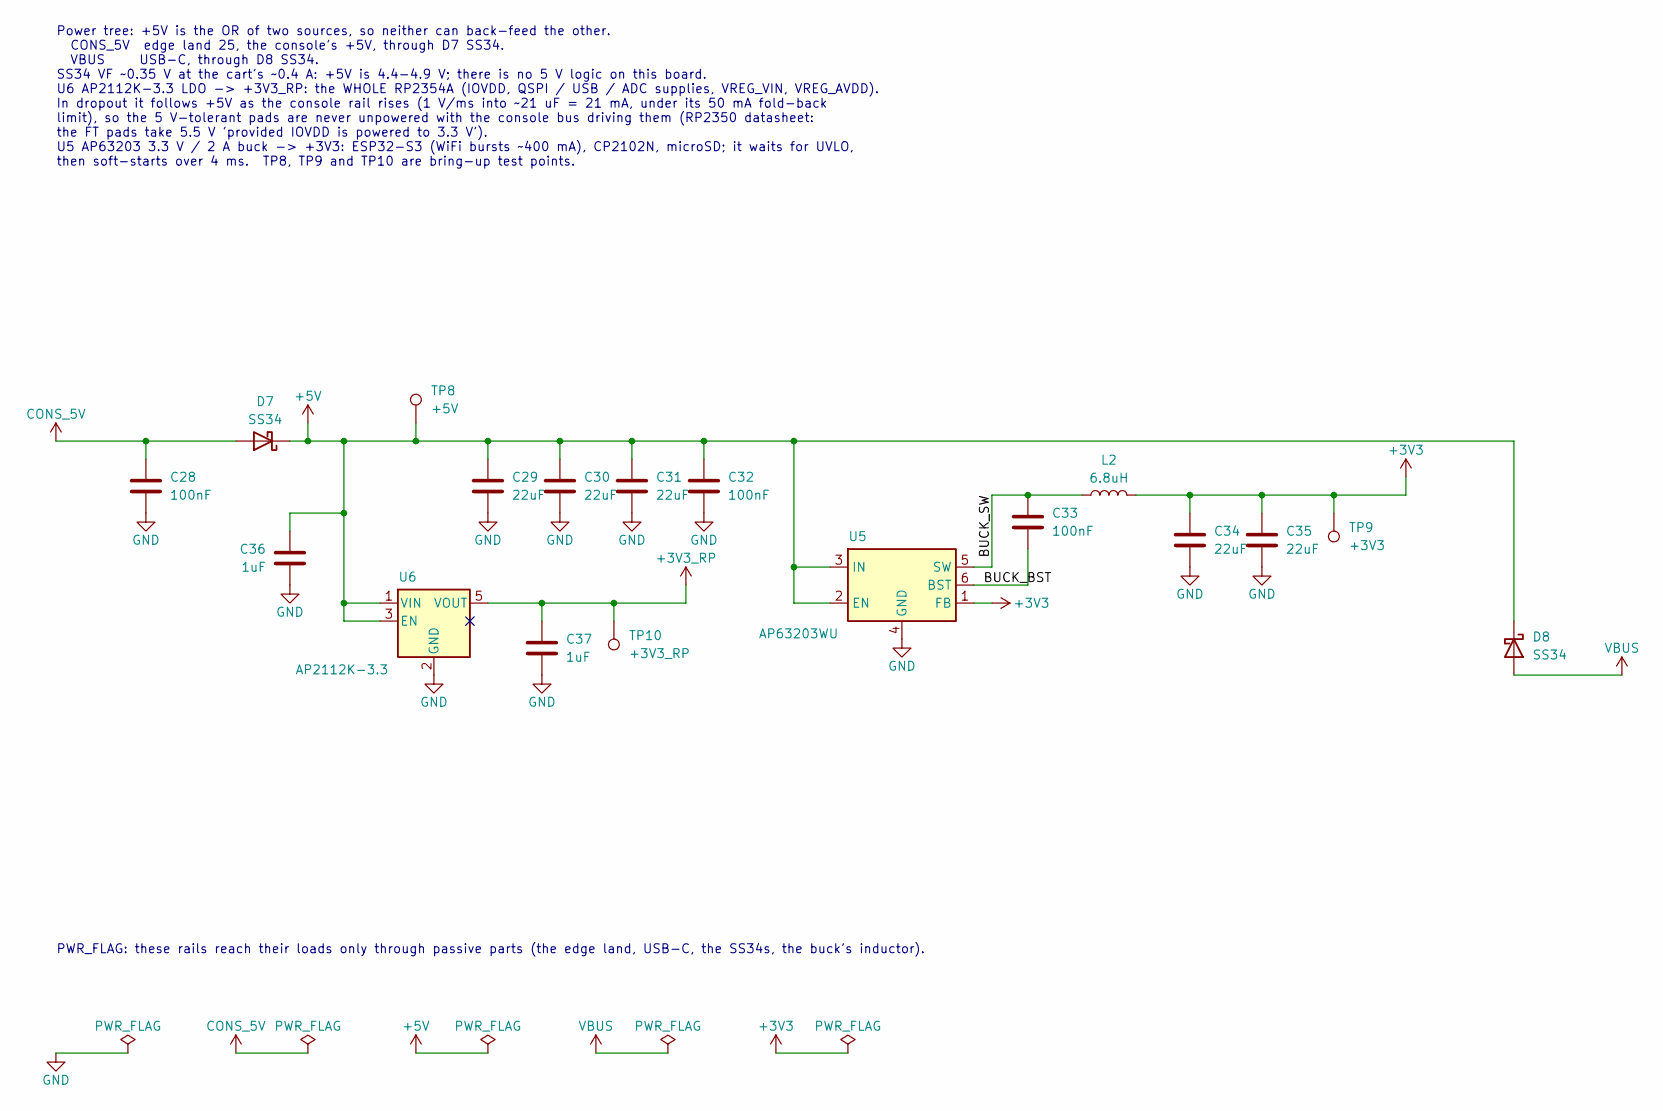
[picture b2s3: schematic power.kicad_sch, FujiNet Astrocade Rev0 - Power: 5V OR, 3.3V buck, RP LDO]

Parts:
C28, C32, C33: 100nF; C_0603_1608Metric; MPN CC0603KRX7R9BB104; LCSC C14663
C29, C30, C31, C34, C35: 22uF; C_0805_2012Metric; MPN CL21A226MAQNNNE; LCSC C45783
C36, C37: 1uF; C_0603_1608Metric; MPN CL10A105KB8NNNC; LCSC C15849
D7, D8: SS34; D_SMA; MPN SS34; LCSC C8678
L2: 6.8uH; L_Sunlord_SWPA4030S; MPN SWPA4030S6R8MT; LCSC C62684
TP8: +5V; TestPoint_Pad_D1.5mm
TP9: +3V3; TestPoint_Pad_D1.5mm
TP10: +3V3_RP; TestPoint_Pad_D1.5mm
U5: AP63203WU; TSOT-23-6; MPN AP63203WU-7; LCSC C780769
U6: AP2112K-3.3; SOT-23-5; MPN AP2112K-3.3TRG1; LCSC C51118

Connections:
+3V3: C34.1, C35.1, L2.2, TP9.1, U5.1 (FB); also elsewhere on the board
+3V3_RP: C37.1, TP10.1, U6.5 (VOUT); also elsewhere on the board
+5V: C29.1, C30.1, C31.1, C32.1, C36.1, D7.1 (K), D8.1 (K), TP8.1, U5.2 (EN), U5.3 (IN), U6.1 (VIN), U6.3 (EN); also elsewhere on the board
/power/BUCK_BST: C33.2, U5.6 (BST)
/power/BUCK_SW: C33.1, L2.1, U5.5 (SW)
CONS_5V: C28.1, D7.2 (A); also elsewhere on the board
GND: C28.2, C29.2, C30.2, C31.2, C32.2, C34.2, C35.2, C36.2, C37.2, U5.4 (GND), U6.2 (GND); also elsewhere on the board
VBUS: D8.2 (A); also elsewhere on the board

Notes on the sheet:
PWR_FLAG: these rails reach their loads only through passive parts (the edge land, USB-C, the SS34s, the buck's inductor).
Power tree: +5V is the OR of two sources, so neither can back-feed the other. CONS_5V edge land 25, the console's +5V, through D7 SS34. VBUS USB-C, through D8 SS34. SS34 VF ~0.35 V at the cart's ~0.4 A: +5V is 4.4-4.9 V; there is no 5 V logic on this board. U6 AP2112K-3.3 LDO -> +3V3_RP: the WHOLE 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

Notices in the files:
Astrocade/rev0/README.md:
Provenance and license:
CERN-OHL-W-2.0.
- **Circuit blocks:** adapted from `FujiNet-INTV-Rev0` in this repository
(itself an adaptation of the PiNTY CARD, CERN-OHL-W-2.0) and the
ESP32-S3-DevKitC-1 v1.1 reference design.
- **Edge pinout:** Jay Tilton (ballyalley.com
`bally_technical_info_(cartridge_port).htm`), cross-checked against MCM
Design's modified cassette cartridge drawing.
- **Blade and physical data:** sakman55's Astrocade cartreader adapter
(github.com/sanni/cartreader discussion #354).
- **RP2350 regulator corner:** Raspberry Pi RP2350A minimal design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
